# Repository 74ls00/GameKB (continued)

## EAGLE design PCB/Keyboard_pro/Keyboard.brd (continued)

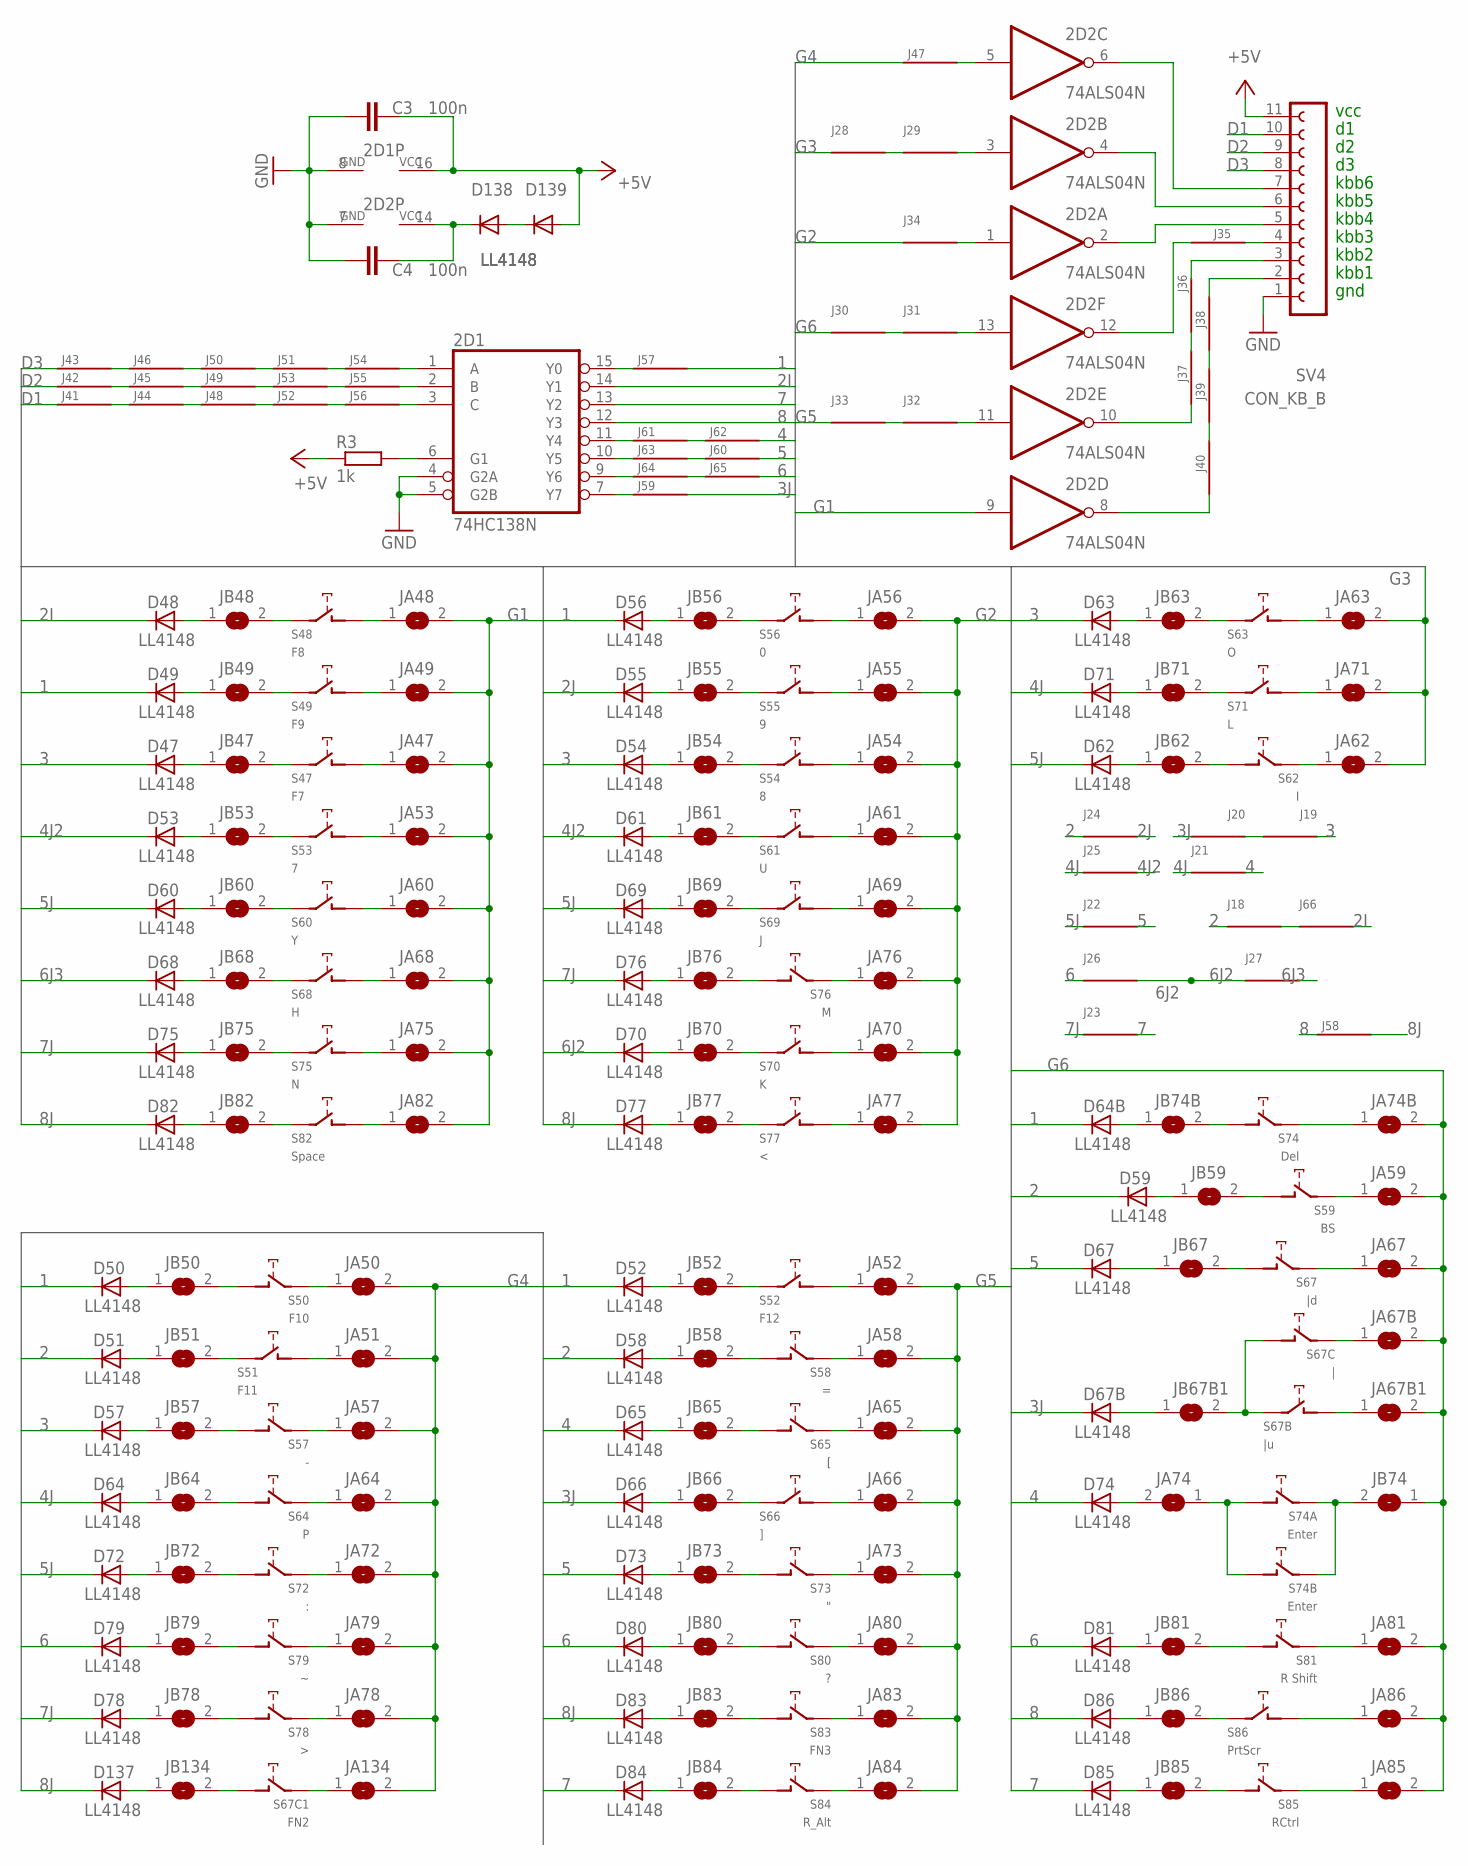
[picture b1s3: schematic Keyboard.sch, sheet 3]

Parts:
2D1: 74HC138N; DIL16
2D2: 74ALS04N; DIL14
C3, C4: 100n; C0805
D47, D48, D49, D50, D51, D52, D53, D54, D55, D56, D57, D58, D59, D60, D61, D62, D63, D64, D64B, D65, D66, D67, D67B, D68, D69, D70, D71, D72, D73, D74, D75, D76, D77, D78, D79, D80, D81, D82, D83, D84, D85, D86, D137, D138, D139: LL4148; SOD80C
J18, J19, J20, J21, J22, J23, J24, J25, J26, J27, J28, J29, J30, J31, J32, J33, J34, J35, J36, J37, J38, J39, J40, J41, J42, J43, J44, J45, J46, J47, J48, J49, J50, J51, J52, J53, J54, J55, J56, J57, J58, J59, J60, J61, J62, J63, J64, J65, J66: J; R1206W
JA47, JA48, JA49, JA50, JA51, JA52, JA53, JA54, JA55, JA56, JA57, JA58, JA59, JA60, JA61, JA62, JA63, JA64, JA65, JA66, JA67, JA67B, JA67B1, JA68, JA69, JA70, JA71, JA72, JA73, JA74, JA74B, JA75, JA76, JA77, JA78, JA79, JA80, JA81, JA82, JA83, JA84, JA85, JA86, JA134: SJ
JB47, JB48, JB49, JB50, JB51, JB52, JB53, JB54, JB55, JB56, JB57, JB58, JB59, JB60, JB61, JB62, JB63, JB64, JB65, JB66, JB67, JB67B1, JB68, JB69, JB70, JB71, JB72, JB73, JB74, JB74B, JB75, JB76, JB77, JB78, JB79, JB80, JB81, JB82, JB83, JB84, JB85, JB86, JB134: SJ
R3: 1k; R0805
S47: F7; CHERRY-MX-4P
S48: F8; CHERRY-MX-4P
S49: F9; CHERRY-MX-4P
S50: F10; CHERRY-MX-4P
S51: F11; CHERRY-MX-4P
S52: F12; CHERRY-MX-4P
S53: 7; CHERRY-MX-4P
S54: 8; CHERRY-MX-4P
S55: 9; CHERRY-MX-4P
S56: 0; CHERRY-MX-4P
S57: -; CHERRY-MX-4P
S58: =; CHERRY-MX-4P
S59: BS; CHERRY-MX-4P
S60: Y; CHERRY-MX-4P
S61: U; CHERRY-MX-4P
S62: I; CHERRY-MX-4P
S63: O; CHERRY-MX-4P
S64: P; CHERRY-MX-4P
S65: [; CHERRY-MX-4P
S66: ]; CHERRY-MX-4P
S67: |d; CHERRY-MX-4P
S67B: |u; CHERRY-MX
S67C: |; CHERRY-MX-4P
S67C1: FN2; CHERRY-MX-4P
S68: H; CHERRY-MX-4P
S69: J; CHERRY-MX-4P
S70: K; CHERRY-MX-4P
S71: L; CHERRY-MX-4P
S72: :; CHERRY-MX-4P
S73: "; CHERRY-MX-4P
S74: Del; CHERRY-MX-4P
S74A: Enter; CHERRY-MX-4P
S74B: Enter; CHERRY-MX
S75: N; CHERRY-MX-4P
S76: M; CHERRY-MX-4P
S77: <; CHERRY-MX-4P
S78: >; CHERRY-MX-4P
S79: CHERRY-MX-4P
S80: ?; CHERRY-MX-4P
S81: R Shift; CHERRY-MX-4P
S82: Space; CHERRY-MX-4P
S83: FN3; CHERRY-MX-4P
S84: R_Alt; CHERRY-MX-4P
S85: RCtrl; CHERRY-MX-4P
S86: PrtScr; CHERRY-MX-4P
SV4: CON_KB_B; FE12

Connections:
1: D49.C, D50.C, D52.C, D56.C, D64B.C, J57.1
2: D51.C, D58.C, D59.C, J18.2, J24.2
2I: 2D1.14 (Y1), D48.C, J66.1
2J: D55.C, J24.1
3: D47.C, D54.C, D57.C, D63.C, J19.2
3J: D66.C, D67B.C, J20.1, J59.1
4: D65.C, D74.C, J21.1, J62.1
4J: D64.C, D71.C, J21.2, J25.2
4J2: D53.C, D61.C, J25.1
5: D67.C, D73.C, J22.1, J60.1
5J: D60.C, D62.C, D69.C, D72.C, J22.2
6: D79.C, D80.C, D81.C, J26.2, J65.1
6J2: D70.C, J26.1, J27.2
6J3: D68.C, J27.1
7: 2D1.13 (Y2), D84.C, D85.C, J23.1
7J: D75.C, D76.C, D78.C, J23.2
8: 2D1.12 (Y3), D86.C, J58.2
8J: D77.C, D82.C, D83.C, D137.C, J58.1
+3VD: 2D2.14 (VCC), C4.1, D138.C
+5V: 2D1.16 (VCC), C3.1, D139.A, R3.1, SV4.11; also elsewhere on the board
D1: J41.2, SV4.10
D2: J42.2, SV4.9
D3: J43.2, SV4.8
G1: 2D2.9 (I), JA47.2, JA48.2, JA49.2, JA53.2, JA60.2, JA68.2, JA75.2, JA82.2; also elsewhere on the board
G2: J34.2, JA54.2, JA55.2, JA56.2, JA61.2, JA69.2, JA70.2, JA76.2, JA77.2; also elsewhere on the board
G3: J28.2, JA62.2, JA63.2, JA71.2
G4: J47.2, JA50.2, JA51.2, JA57.2, JA64.2, JA72.2, JA78.2, JA79.2, JA134.2
G5: J33.2, JA52.2, JA58.2, JA65.2, JA66.2, JA73.2, JA80.2, JA83.2, JA84.2
G6: J30.2, JA59.2, JA67.2, JA67B.2, JA67B1.2, JA74B.2, JA81.2, JA85.2, JA86.2, JB74.1
GND: 2D1.4 (G2A), 2D1.5 (G2B), 2D1.8 (GND), 2D2.7 (GND), C3.2, C4.2, SV4.1; also elsewhere on the board
unnamed: JA67B1.1, S67B.SW2 (PIN-2)
unnamed: JB52.2, S52.SW1 (PIN-1)
unnamed: JB63.2, S63.SW1 (PIN-1)
unnamed: JA67B.1, S67C.SW1 (PIN-1)
unnamed: JB74.2, S74A.SW1 (PIN-1), S74B.SW1 (PIN-1)
unnamed: JA74.1, S74A.SW2 (PIN-2), S74B.SW2 (PIN-2)
unnamed: JB47.2, S47.SW1 (PIN-1)
unnamed: JB53.2, S53.SW1 (PIN-1)
unnamed: JB74B.2, S74.SW2 (PIN-2)
unnamed: JB60.2, S60.SW1 (PIN-1)
unnamed: JB68.2, S68.SW1 (PIN-1)
unnamed: JB75.2, S75.SW1 (PIN-1)
unnamed: JB82.2, S82.SW1 (PIN-1)
unnamed: JB48.2, S48.SW1 (PIN-1)
unnamed: JB54.2, S54.SW1 (PIN-1)
unnamed: JB61.2, S61.SW1 (PIN-1)
unnamed: JB69.2, S69.SW1 (PIN-1)
unnamed: JB67B1.2, S67B.SW1 (PIN-1), S67C.SW2 (PIN-2)
unnamed: JA134.1, S67C1.SW1 (PIN-1)
unnamed: JB49.2, S49.SW1 (PIN-1)
unnamed: JB55.2, S55.SW1 (PIN-1)
unnamed: JB134.2, S67C1.SW2 (PIN-2)
unnamed: JB70.2, S70.SW1 (PIN-1)
unnamed: JB77.2, S77.SW1 (PIN-1)
unnamed: D137.A, JB134.1
unnamed: JB50.2, S50.SW2 (PIN-2)
unnamed: JB56.2, S56.SW1 (PIN-1)
unnamed: D67B.A, JB67B1.1
unnamed: JB78.2, S78.SW2 (PIN-2)
unnamed: JB85.2, S85.SW2 (PIN-2)
unnamed: JB51.2, S51.SW1 (PIN-1)
unnamed: JB83.2, S83.SW2 (PIN-2)
unnamed: JB73.2, S73.SW2 (PIN-2)
unnamed: JA73.1, S73.SW1 (PIN-1)
unnamed: JB79.2, S79.SW2 (PIN-2)
unnamed: JB57.2, S57.SW2 (PIN-2)
unnamed: JB58.2, S58.SW2 (PIN-2)
unnamed: JB65.2, S65.SW2 (PIN-2)
unnamed: JA80.1, S80.SW1 (PIN-1)
unnamed: JB59.2, S59.SW2 (PIN-2)
unnamed: JB66.2, S66.SW1 (PIN-1)
unnamed: JB67.2, S67.SW2 (PIN-2)
unnamed: JB81.2, S81.SW2 (PIN-2)
unnamed: D47.A, JB47.1
unnamed: D53.A, JB53.1
unnamed: D60.A, JB60.1
unnamed: D68.A, JB68.1
unnamed: D75.A, JB75.1
unnamed: D82.A, JB82.1
unnamed: D48.A, JB48.1
unnamed: D54.A, JB54.1
unnamed: D61.A, JB61.1
unnamed: D69.A, JB69.1
unnamed: D76.A, JB76.1
unnamed: D83.A, JB83.1
unnamed: D49.A, JB49.1
unnamed: D55.A, JB55.1
unnamed: D62.A, JB62.1
unnamed: D70.A, JB70.1
unnamed: D77.A, JB77.1
unnamed: D84.A, JB84.1
unnamed: D50.A, JB50.1
unnamed: D56.A, JB56.1
unnamed: D63.A, JB63.1
unnamed: D71.A, JB71.1
unnamed: D78.A, JB78.1
unnamed: D85.A, JB85.1
unnamed: D51.A, JB51.1
unnamed: D57.A, JB57.1
unnamed: D64.A, JB64.1
unnamed: D72.A, JB72.1
unnamed: D79.A, JB79.1
unnamed: D86.A, JB86.1
unnamed: D52.A, JB52.1
unnamed: D58.A, JB58.1
unnamed: D65.A, JB65.1
unnamed: D73.A, JB73.1
unnamed: D80.A, JB80.1
unnamed: D59.A, JB59.1
unnamed: D66.A, JB66.1
unnamed: D67.A, JB67.1
unnamed: D74.A, JA74.2
unnamed: D81.A, JB81.1
unnamed: JA66.1, S66.SW2 (PIN-2)
unnamed: JA47.1, S47.SW2 (PIN-2)
unnamed: JA53.1, S53.SW2 (PIN-2)
unnamed: JA60.1, S60.SW2 (PIN-2)
unnamed: JA68.1, S68.SW2 (PIN-2)
unnamed: JA75.1, S75.SW2 (PIN-2)
unnamed: JA82.1, S82.SW2 (PIN-2)
unnamed: JA48.1, S48.SW2 (PIN-2)
unnamed: JA54.1, S54.SW2 (PIN-2)
unnamed: JA61.1, S61.SW2 (PIN-2)
unnamed: JA69.1, S69.SW2 (PIN-2)
unnamed: JA57.1, S57.SW1 (PIN-1)
unnamed: JA83.1, S83.SW1 (PIN-1)
unnamed: JA49.1, S49.SW2 (PIN-2)
unnamed: JA55.1, S55.SW2 (PIN-2)
unnamed: JA64.1, S64.SW1 (PIN-1)
unnamed: JA70.1, S70.SW2 (PIN-2)
unnamed: JA77.1, S77.SW2 (PIN-2)
unnamed: JB80.2, S80.SW2 (PIN-2)
unnamed: JA50.1, S50.SW1 (PIN-1)
unnamed: JA56.1, S56.SW2 (PIN-2)
unnamed: JA63.1, S63.SW2 (PIN-2)
unnamed: J19.1, J20.2
unnamed: JA78.1, S78.SW1 (PIN-1)
unnamed: JA85.1, S85.SW1 (PIN-1)
unnamed: JA51.1, S51.SW2 (PIN-2)
unnamed: JB64.2, S64.SW2 (PIN-2)
unnamed: JB72.2, S72.SW2 (PIN-2)
unnamed: JA72.1, S72.SW1 (PIN-1)
unnamed: JA79.1, S79.SW1 (PIN-1)
unnamed: JB62.2, S62.SW2 (PIN-2)
unnamed: JA52.1, S52.SW2 (PIN-2)
unnamed: JA65.1, S65.SW1 (PIN-1)
unnamed: JA58.1, S58.SW1 (PIN-1)
unnamed: JB84.2, S84.SW2 (PIN-2)
unnamed: JA84.1, S84.SW1 (PIN-1)
unnamed: JA81.1, S81.SW1 (PIN-1)
unnamed: JA67.1, S67.SW1 (PIN-1)
unnamed: JA59.1, S59.SW1 (PIN-1)
unnamed: D64B.A, JB74B.1
unnamed: JA74B.1, S74.SW1 (PIN-1)
unnamed: JA62.1, S62.SW1 (PIN-1)
unnamed: JB71.2, S71.SW1 (PIN-1)
unnamed: JA71.1, S71.SW2 (PIN-2)
unnamed: 2D1.6 (G1), R3.2
unnamed: JB76.2, S76.SW2 (PIN-2)
unnamed: JA76.1, S76.SW1 (PIN-1)
unnamed: 2D2.6 (O), SV4.7
unnamed: 2D2.4 (O), SV4.6
unnamed: 2D2.2 (O), SV4.5
unnamed: 2D2.12 (O), J35.2
unnamed: 2D2.8 (O), J40.2
unnamed: J28.1, J29.2
unnamed: 2D2.3 (I), J29.1
unnamed: J30.1, J31.2
unnamed: 2D2.13 (I), J31.1
unnamed: J32.2, J33.1
unnamed: 2D2.11 (I), J32.1
unnamed: 2D2.1 (I), J34.1
unnamed: J35.1, SV4.4
unnamed: J36.1, SV4.3
unnamed: J36.2, J37.1
unnamed: 2D2.10 (O), J37.2
unnamed: J38.1, SV4.2
unnamed: J38.2, J39.1
unnamed: J39.2, J40.1
unnamed: D138.A, D139.C
unnamed: J41.1, J44.2
unnamed: J42.1, J45.2
unnamed: J43.1, J46.2
unnamed: 2D2.5 (I), J47.1
unnamed: J44.1, J48.2
unnamed: J45.1, J49.2
unnamed: J46.1, J50.2
unnamed: J50.1, J51.2
unnamed: J48.1, J52.2
unnamed: J49.1, J53.2
unnamed: J51.1, J54.2
unnamed: J53.1, J55.2
unnamed: J52.1, J56.2
unnamed: 2D1.1 (A), J54.1
unnamed: 2D1.2 (B), J55.1
unnamed: 2D1.3 (C), J56.1
unnamed: 2D1.15 (Y0), J57.2
unnamed: JB86.2, S86.SW1 (PIN-1)
unnamed: JA86.1, S86.SW2 (PIN-2)
unnamed: 2D1.7 (Y7), J59.2
unnamed: J61.1, J62.2
unnamed: 2D1.11 (Y4), J61.2
unnamed: J60.2, J63.1
unnamed: J64.1, J65.2
unnamed: 2D1.9 (Y6), J64.2
unnamed: 2D1.10 (Y5), J63.2
unnamed: J18.1, J66.2

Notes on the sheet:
kbb6
kbb5
kbb4
kbb3
kbb2
kbb1
gnd
vcc

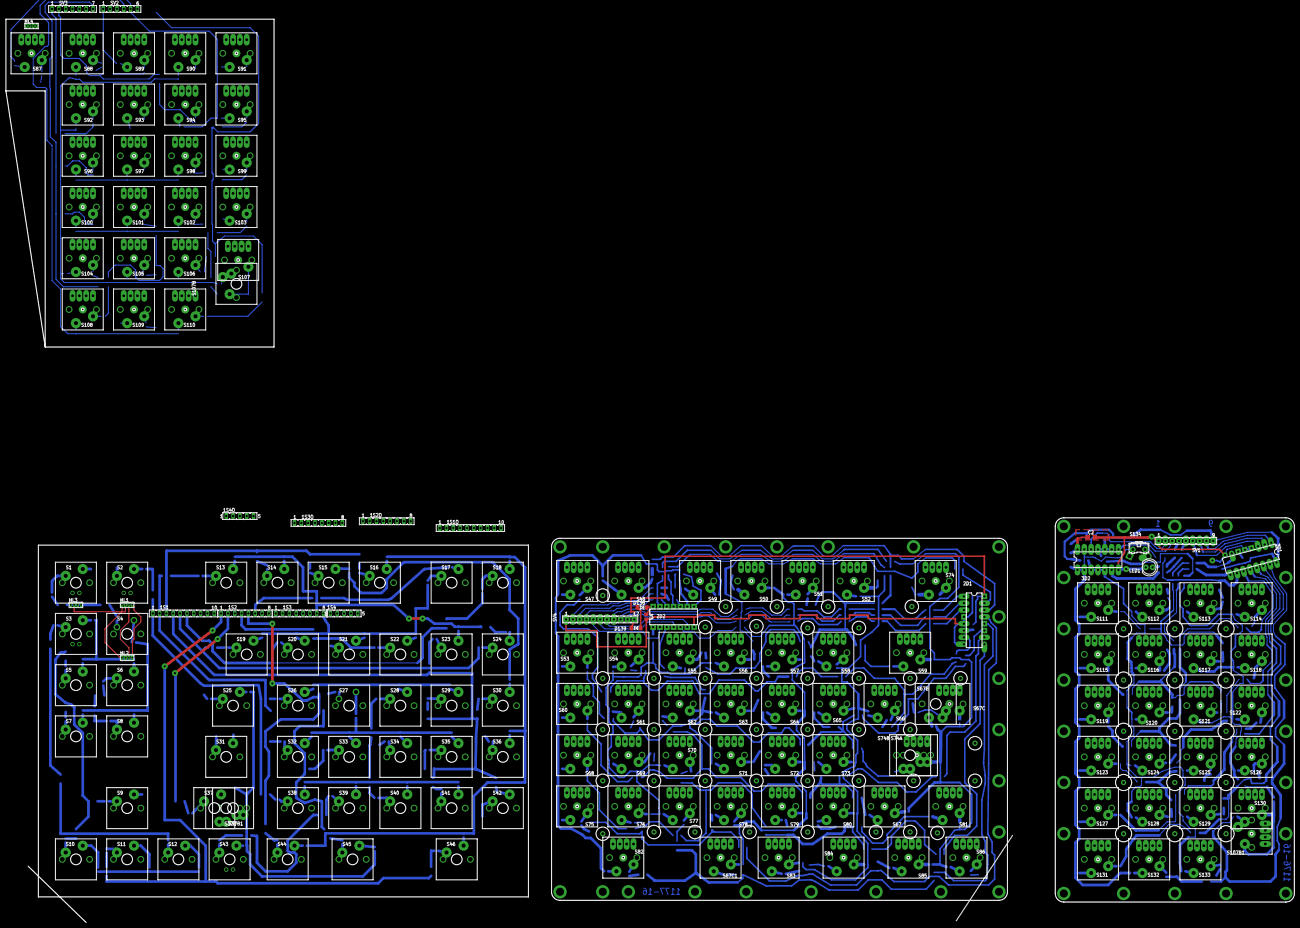
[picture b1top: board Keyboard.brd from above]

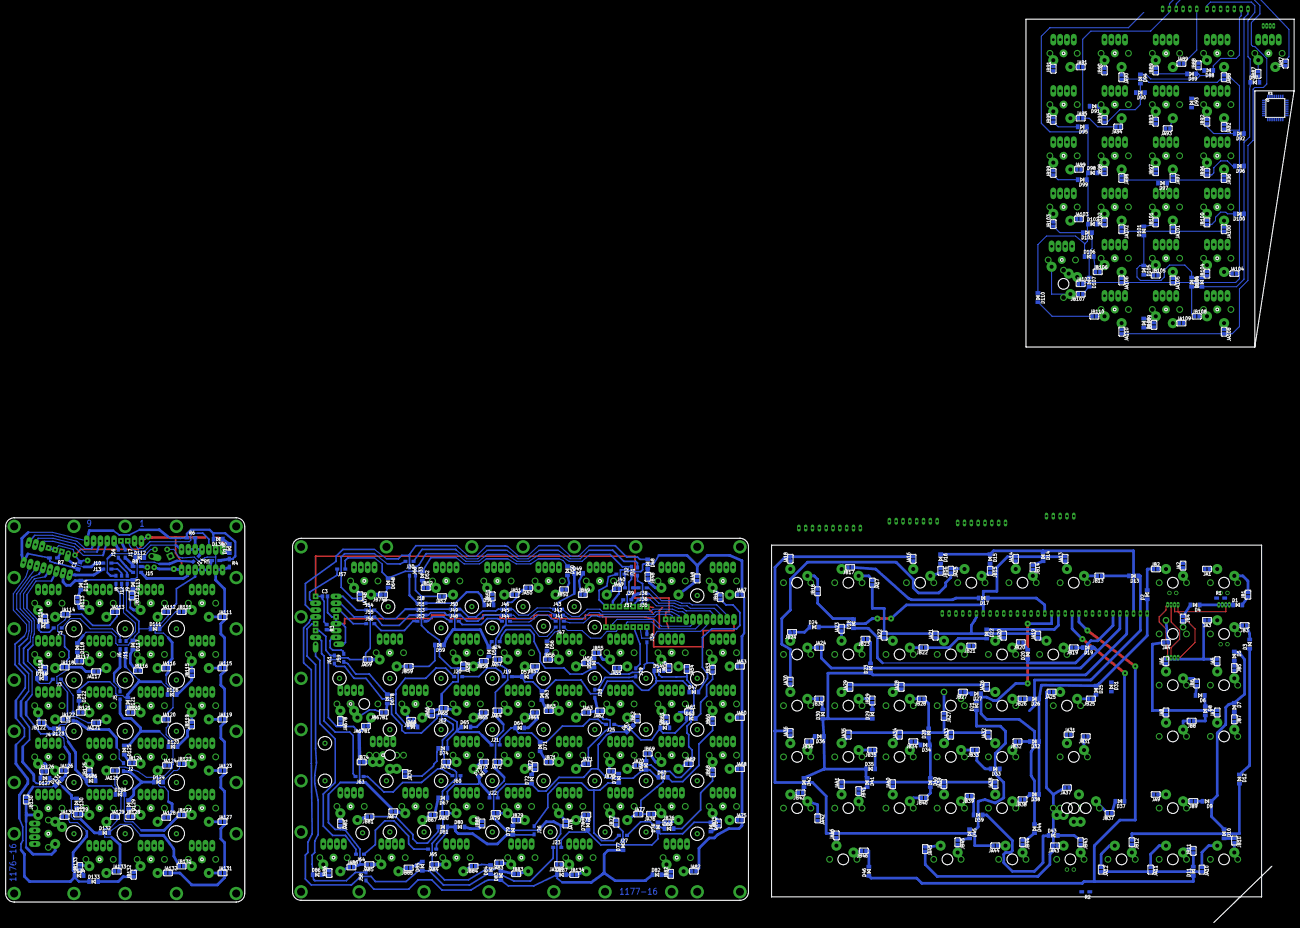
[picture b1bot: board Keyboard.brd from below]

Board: 2 copper layers, 479.1 x 335.9 mm, 825 parts (57 on the bottom side), 571 nets.

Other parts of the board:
U$1, U$2, U$3, U$4, U$5, U$6, U$7, U$8, U$9, U$10, U$11, U$12, U$13, U$14, U$18, U$19, U$20, U$21, U$23, U$24, U$25, U$26, U$27, U$29, U$30, U$31, U$32, U$33, U$35, U$36, U$37, U$38, U$39, U$40, U$41, U$42, U$43, U$44, U$45, U$46, U$47, U$48, U$49, U$50, U$51, U$52, U$53, U$54, U$55, U$56, U$57, U$58, U$59, U$60, U$61, U$62, U$63, U$64, U$65, U$66, U$67, U$68, U$69, U$70, U$71, U$72, U$73, U$74, U$75, U$76, U$77, U$78, U$81, U$82, U$83, U$87, U$88, U$89, U$90, U$91, U$92, U$93, U$94, U$95, U$96, U$97, U$98, U$99, U$100, U$101, U$102, U$103, U$104, U$105, U$106, U$107, U$108, U$109, U$110, U$116, U$117, U$118, U$119, U$120, U$121, U$122, U$123, U$124, U$125, U$126, U$127, U$128, U$129, U$130, U$131, U$132, U$133, U$134, U$135, U$136, U$137, U$138, U$139, U$141, U$215: 18X18
U$15, U$16, U$84, U$85, U$86: 18X23
U$17, U$79: 18X52
U$22, U$213: 18X42
U$28, U$114: 18X33
U$34, U$115, U$214, U$216, U$217: 18X28
U$80, U$112: 18X37
U$111, U$140: 37X18
U$142, U$143, U$144, U$145, U$146, U$147, U$148, U$150, U$151, U$152, U$153, U$154, U$155, U$156, U$157, U$158, U$159, U$160, U$161, U$162, U$163, U$164: KEY
U$149: NUMENTER
